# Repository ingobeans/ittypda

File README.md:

# ittyPDA

hi! this is my little thing im working on.

ittyPDA is an itty-bitty PDA/cyberdeck thingy. its smaller than a nintendo ds but has a real keyboard and a full color IPS LCD display, powered by an STM32 microcontroller. its my first ever hardware project and first time designing a pcb !!

it's mainly intended for note-taking/writing, playing silly little videogames, and just being a very hackable little computer.

this repo contains both the hardware designs, under the `ittypda/` subdirectory, as well as the operating system under `ittyOS/`. 3D case files are under `case/`.

## specs & parts

* microprocessor: [STM32F411RET6](https://www.st.com/en/microcontrollers-microprocessors/stm32f411re.html)
    * Up to 100 MHz
    * 512 Kb flash
    * 128 Kb RAM
* display: [3.5" IPS display (no touch version)](https://www.lcdwiki.com/3.5inch_IPS_SPI_Module_ST7796)
* storage: SD card slot included on display
* charging/data transfer possible over USB-C
* battery: 2200mAh LiPo - [this is the one I use, but really any battery with a similar size and connector will work](https://www.amazon.se/-/en/gp/product/B0D7VT93JX?smid=A2YUU8D7JQVZCY&th=1)
* on-board charging circuitry powered by a [BQ24040DSQR](https://www.ti.com/product/BQ24040)
    * also battery level sensing

## download symbols/footprints

to open the kicad project, youll need to download some footprints. my parts are sourced from JLCPCB's parts / LCSC, and you can use [`easyeda2kicad`](https://github.com/uPesy/easyeda2kicad.py) to download LCSC parts to kicad.

the command you need to run is: 

```bash
easyeda2kicad --full --lcsc_id C318884 C191023 C22435642 C13738 C81080 C49023767 C19273152 C165948 C295747 C20416998 C2682616
```

which will download footprints/symbols/3d models for the switches, diodes, etc.

## project status (important !!)

project is in a very early WIP state currently! the PCB is the only truly *finished* part so far.

the case is just a minimum-viable-product for now, and the firmware mostly acts as a proof-of-concept regarding graphics streaming and input handling from the keyboard matrix.

thus the project is mostly about the creation of the PCB, with the case and firmware mostly just acting as beta features used to test the PCB itself.

these features will be developed in the coming months though, and when i have guaranteed that the core PCB does work! this is a project i intend to gradually work on for a long time !

## schematic / PCB

the schematic and PCB are designed in KiCad, files for which are found in `ittypda/`.

the PCB is split in two seperate parts. this is done to achieve a budget 4-layer board, and to get around the fact that JLCPCB's economy PCBA service cant assemble parts on the bottomside of the board.

the mainboard houses the microcontroller, the keypad, and display connector.

the secondary board houses the usb-c port, battery charging ic, voltage regulator, etc.

the two boards mount together like a PCB-sandwich and connect through 7 soldered pads.

showcase how the two boards are mounted:

## firmware - ittyOS

ittyOS is currently in an early proof of concept state, but will have many different apps later on.

implemented:
* display drivers
* reading from microSD card
* streaming image data from microSD to screen
* input from keyboard
* program switching
* basic home screen
* basic notes app

todo:
* improve text input
* usb file transfer
* more apps!
    * wordle
    * journal
* different themes?

### compile ittyOS

the `../firmware` folder contains the low level hardware setup for different boards that can run ittyOS, while `ittyOS/` contains the shared code and the actual system, which is then linked to from the firmware.

you'll need to generate the firmware code from the STM32 project file, since the low-level drivers for these boards are very large and therefore gitignored. you'll need STM32CubeMX. then just open the project file for the firmware you want to build, and hit generate code. 

you'll also have to tell your LSP which CMakeLists you're using.

then, to build, navigate to the firmware you want to build's directory.

1. `cmake --preset Debug` (you only have to run this once)
2. `cmake --build --preset Debug`
3. `STM32_Programmer_CLI -c port=swd -w build/Debug/<DEVBOARD OR ITTYPDA HERE>.elf -v -rst`

## case

the case files are located under `case/`.

the case is designed in,.. blender. its mostly a MVP for a case, and when i get the phyiscal PCB, this and the firmware will be the major focus for the project moving forwards.

most parts are designed to friction-fit, though i wont know how well this works in practice, but will find out soon !

## BOMs

### Final bom (bom.csv)

|Name                         |Cost ($)                              |Source                                                                                           |
|-----------------------------|--------------------------------------|-------------------------------------------------------------------------------------------------|
|PCB                          |13.43                                 |JLCPCB                                                                                           |
|PCB Assembly Fees            |48.21                                 |JLCPCB                                                                                           |
|PCB Assembly Components      |20.55                                 |JLCPCB                                                                                           |
|PCB Shipping                 |24.07                                 | DHL Express                                                                                     |
|Customs & taxes              | 26.56                                |                                                                                                 |
|Total                        |132.77                                |                                                                                                 |

### Parts bom (parts-bom.csv)

|Part Name                    |Description                           |Link                                                                                             |Quantity                                                            |Total Price ($)                                                        |
|-----------------------------|--------------------------------------|-------------------------------------------------------------------------------------------------|--------------------------------------------------------------------|-----------------------------------------------------------------------|
|CL05B104KO5NNNC              |100nF 0402 Ceramic Capacitors         |https://jlcpcb.com/partdetail/1877-CL05B104KO5NNNC/C1525                                         |16                                                                  |0.0864                                                                 |
|CL05A475MP5NRNC              |10V 0402 Ceramic Capacitors           |https://jlcpcb.com/partdetail/24469-CL05A475MP5NRNC/C23733                                       |4                                                                   |0.0828                                                                 |
|CL05C100JB5NNNC              |10pF 0402 Ceramic Capacitors          |https://jlcpcb.com/partdetail/33914-CL05C100JB5NNNC/C32949                                       |4                                                                   |0.0212                                                                 |
|CL05A105KA5NQNC              |1uF 0402 Ceramic Capacitors           |https://jlcpcb.com/partdetail/53938-CL05A105KA5NQNC/C52923                                       |8                                                                   |0.1272                                                                 |
|CL05A225MQ5NSNC              |2.2uF 0402 Ceramic Capacitors         |https://jlcpcb.com/partdetail/13164-CL05A225MQ5NSNC/C12530                                       |2                                                                   |0.0128                                                                 |
|S2B-PH-SM4-TB(LF)(SN)        |PH JST Connector 2mm                  |https://jlcpcb.com/partdetail/JST-S2B_PH_SM4_TB_LF_SN/C295747                                    |2                                                                   |0.427                                                                  |
|1N5819WS                     |Schottky Diodes                       |https://jlcpcb.com/partdetail/GuangdongHottech-1N5819WS/C191023                                  |114                                                                 |1.5504                                                                 |
|05A20L14P                    |FPC Connector                         |https://jlcpcb.com/partdetail/HanElectricity-05A20L14P/C22435642                                 |2                                                                   |0.1404                                                                 |
|TYPE-C-31-M-12               |USB-C Connectors                      |https://jlcpcb.com/partdetail/Korean_HropartsElec-TYPE_C_31_M12/C165948                          |2                                                                   |0.3686                                                                 |
|YLED0603Y                    |Yellow 0603 LED                       |https://jlcpcb.com/partdetail/YONGYUTAI-YLED0603Y/C19273152                                      |20                                                                  |0.13                                                                   |
|0402WGF1002TCE               |10k ohm 0402 Resistor                 |https://jlcpcb.com/partdetail/26487-0402WGF1002TCE/C25744                                        |2                                                                   |0.023                                                                  |
|0402WGF5101TCE               |5.1k ohm 0402 Resistor                |https://jlcpcb.com/partdetail/26648-0402WGF5101TCE/C25905                                        |4                                                                   |0.0268                                                                 |
|0402WGF5100TCE               |510 ohm 0402 Resistor                 |https://jlcpcb.com/partdetail/25866-0402WGF5100TCE/C25123                                        |2                                                                   |0.0122                                                                 |
|0402WGF1001TCE               |1k ohm 0402 Resistor                  |https://jlcpcb.com/partdetail/12256-0402WGF1001TCE/C11702                                        |4                                                                   |0.0392                                                                 |
|0402WGF100JTCE               |10 ohm 0402 Resistor                  |https://jlcpcb.com/partdetail/25820-0402WGF100JTCE/C25077                                        |6                                                                   |0.0342                                                                 |
|TS-1187A-B-A-B               |Tactile Switches                      |https://jlcpcb.com/partdetail/XKBConnection-TS_1187A_B_AB/C318884                                |116                                                                 |2.3664                                                                 |
|MST-12D18G4 SPDT             | Slide Switch                         |https://jlcpcb.com/partdetail/C49023767                                                          |2                                                                   |0.1654                                                                 |
|MAX17048G+T10                |Battery Sense IC MAX17048GT10         |https://jlcpcb.com/partdetail/2777647-MAX17048GT10/C2682616                                      |2                                                                   |4.3212                                                                 |
|BQ24040DSQR                  |Lithium Battery Charge IC BQ24040DSQR |https://jlcpcb.com/partdetail/TexasInstruments-BQ24040DSQR/C81080                                |5                                                                   |2.243                                                                  |
|TLV76133DCYR                 |3.3V Fixed Voltage Regulators - Linear|https://jlcpcb.com/partdetail/TexasInstruments-TLV76133DCYR/C7527500                             |2                                                                   |0.438                                                                  |
|STM32F411RET6                |Microcontroller                       |https://jlcpcb.com/partdetail/STMicroelectronics-STM32F411RET6/C94355                            |2                                                                   |7.7452                                                                 |
|X322516MLB4SI                |16MHz 9pF Crystal Oscillator          |https://jlcpcb.com/partdetail/YXC_CrystalOscillators-X322516MLB4SI/C13738                        |2                                                                   |0.1856                                                                 |

<hr>

<sup>no ai usage</sup>

<sup>made with <3</sup>

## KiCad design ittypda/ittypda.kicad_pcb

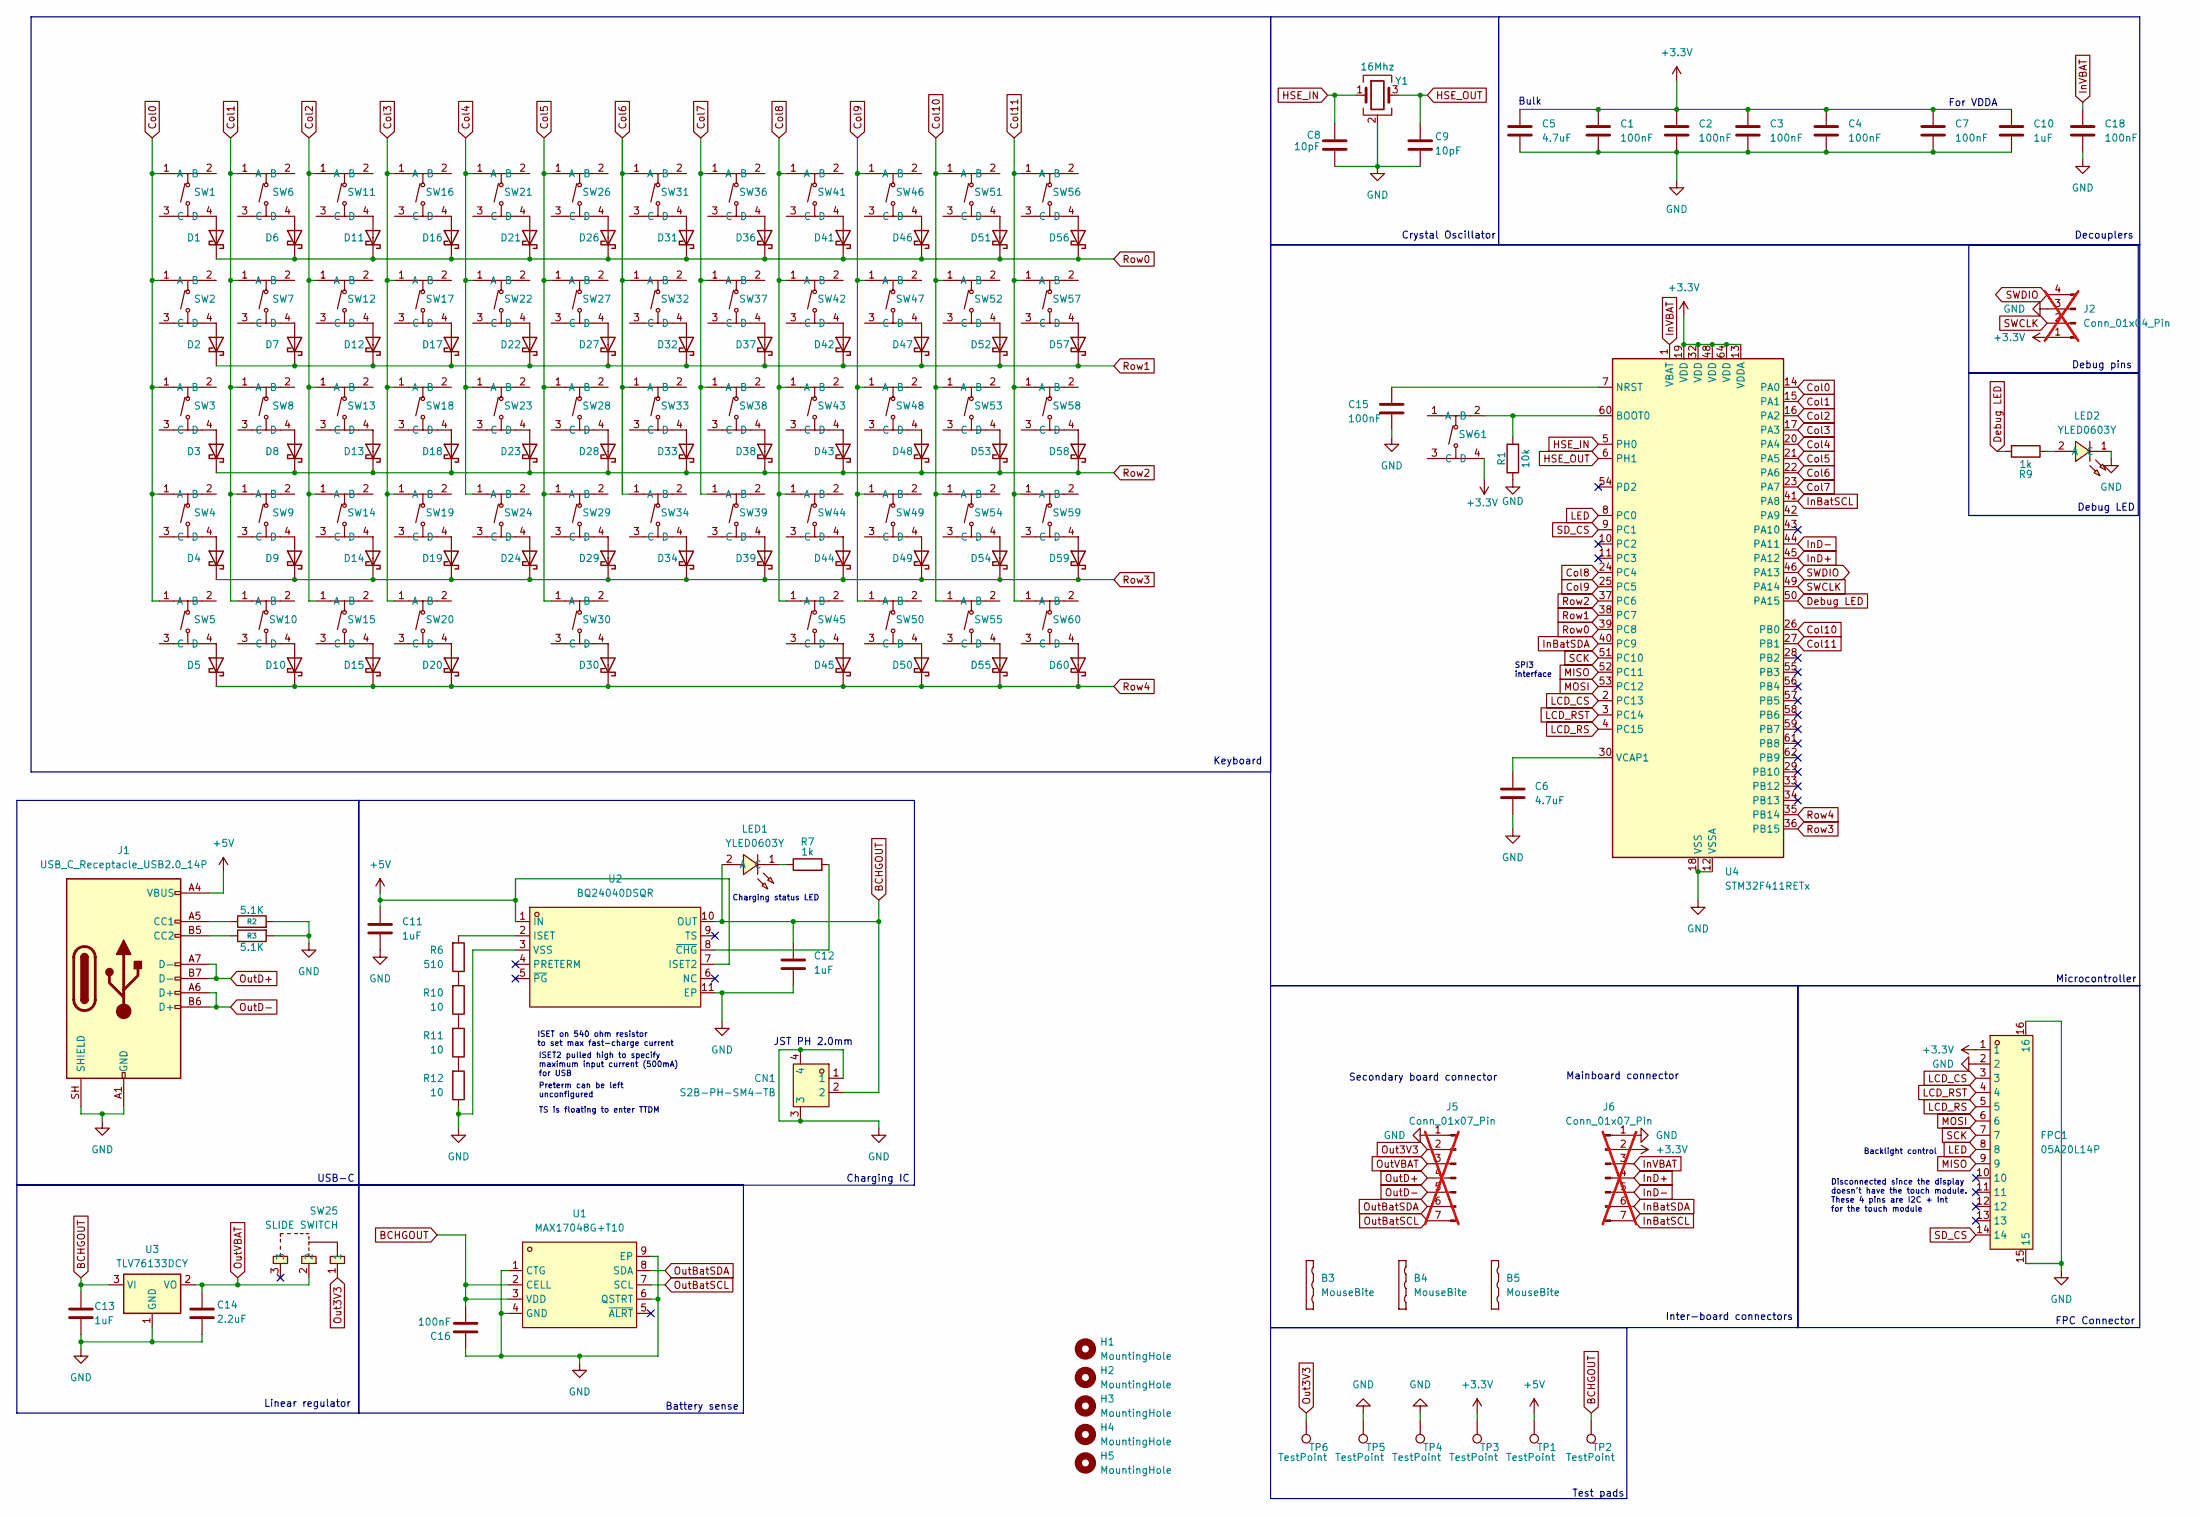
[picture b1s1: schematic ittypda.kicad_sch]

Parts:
B3, B4, B5: MouseBite; mouse-bite-3mm-slot
C1, C2, C3, C4, C7, C15, C16, C18: 100nF; C_0402_1005Metric
C5, C6: 4.7uF; C_0402_1005Metric
C8, C9: 10pF; C_0402_1005Metric
C10, C11, C12, C13: 1uF; C_0402_1005Metric
C14: 2.2uF; C_0402_1005Metric
CN1: S2B-PH-SM4-TB; CONN-SMD_P2.00_S2B-PH-SM4-TB-LF-SN; MPN S2B-PH-SM4-TB(LF)(SN); LCSC Part C295747
D1, D2, D3, D4, D5, D6, D7, D8, D9, D10, D11, D12, D13, D14, D15, D16, D17, D18, D19, D20, D21, D22, D23, D24, D26, D27, D28, D29, D30, D31, D32, D33, D34, D36, D37, D38, D39, D41, D42, D43, D44, D45, D46, D47, D48, D49, D50, D51, D52, D53, D54, D55, D56, D57, D58, D59, D60: 1N5819WS; SOD-323_L1.8-W1.3-LS2.5-RD; Forward Voltage (Vf@If) 600mV@1A; Reverse Voltage (Vr) 40V; Part 1N5819WS; LCSC C191023
FPC1: 05A20L14P; CONN-SMD_05A20L14P; MPN 05A20L14P; LCSC Part C22435642
H1, H2, H3, H4, H5: MountingHole; ToolingHole_1.152mm
J1: USB_C_Receptacle_USB2.0_14P; USB_C_Receptacle_HRO_TYPE-C-31-M-12; LCSC Part C165948
J2: Conn_01x04_Pin; PinHeader_1x04_P2.54mm_Vertical; not fitted
J5, J6: Conn_01x07_Pin; PinHeader_1x07_P2.54mm_Vertical; not fitted
LED1, LED2: YLED0603Y; LED0603-RD-1; MPN YLED0603Y; LCSC Part C19273152
R1: 10k; R_0402_1005Metric
R2, R3: 5.1K; R_0402_1005Metric
R6: 510; R_0402_1005Metric
R7, R9: 1k; R_0402_1005Metric
R10, R11, R12: 10; R_0402_1005Metric
SW1, SW2, SW3, SW4, SW5, SW6, SW7, SW8, SW9, SW10, SW11, SW12, SW13, SW14, SW15, SW16, SW17, SW18, SW19, SW20, SW21, SW22, SW23, SW24, SW26, SW27, SW28, SW29, SW30, SW31, SW32, SW33, SW34, SW36, SW37, SW38, SW39, SW41, SW42, SW43, SW44, SW45, SW46, SW47, SW48, SW49, SW50, SW51, SW52, SW53, SW54, SW55, SW56, SW57, SW58, SW59, SW60, SW61: Switch; SW-SMD_4P-L5.1-W5.1-P3.70-LS6.5-TL_H1.5; MPN TS-1187A-B-A-B; LCSC Part C318884
SW25: SLIDE SWITCH; SW-SMD_MST-12D18G4-SPDT-SLIDE-SWITCH; MPN MST-12D18G2 SMD Slide Switch; LCSC Part C49023767
TP1, TP2, TP3, TP4, TP5, TP6: TestPoint; TestPoint_Pad_D1.5mm
U1: MAX17048G+T10; TDFN-8_L2.0-W2.0-P0.50-BL-EP1.2; MPN MAX17048G+T10; LCSC Part C2682616
U2: BQ24040DSQR; WSON-10_L2.0-W2.0-P0.40-BL-EP; MPN BQ24040DSQR; LCSC Part C81080
U3: TLV76133DCY; SOT-223-3_TabPin2
U4: STM32F411RETx; LQFP-64_10x10mm_P0.5mm
Y1: 16Mhz; CRYSTAL-SMD_4P-L3.2-W2.5-BL

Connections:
+3.3V: C1.1, C2.1, C3.1, C4.1, C5.1, C7.1, C10.1, FPC1.1, J2.1, J6.2, SW61.4 (D), TP3.1 (1_1), U4.13 (VDDA), U4.19 (VDD), U4.32 (VDD), U4.48 (VDD), U4.64 (VDD)
+5V: C11.1, J1.A4 (VBUS), J1.A9 (VBUS), J1.B4 (VBUS), J1.B9 (VBUS), TP1.1 (1_1), U2.1 (IN), U2.7 (ISET2)
BCHGOUT: C12.1, C13.1, C16.2, CN1.2, LED1.2 (A), TP2.1 (1_1), U1.2 (CELL), U1.3 (VDD), U2.10 (OUT), U3.3 (VI)
Col0: SW1.1 (A), SW2.1 (A), SW3.1 (A), SW4.1 (A), SW5.1 (A), U4.14 (PA0)
Col1: SW6.1 (A), SW7.1 (A), SW8.1 (A), SW9.1 (A), SW10.1 (A), U4.15 (PA1)
Col2: SW11.1 (A), SW12.1 (A), SW13.1 (A), SW14.1 (A), SW15.1 (A), U4.16 (PA2)
Col3: SW16.1 (A), SW17.1 (A), SW18.1 (A), SW19.1 (A), SW20.1 (A), U4.17 (PA3)
Col4: SW21.1 (A), SW22.1 (A), SW23.1 (A), SW24.1 (A), U4.20 (PA4)
Col5: SW26.1 (A), SW27.1 (A), SW28.1 (A), SW29.1 (A), SW30.1 (A), U4.21 (PA5)
Col6: SW31.1 (A), SW32.1 (A), SW33.1 (A), SW34.1 (A), U4.22 (PA6)
Col7: SW36.1 (A), SW37.1 (A), SW38.1 (A), SW39.1 (A), U4.23 (PA7)
Col8: SW41.1 (A), SW42.1 (A), SW43.1 (A), SW44.1 (A), SW45.1 (A), U4.24 (PC4)
Col9: SW46.1 (A), SW47.1 (A), SW48.1 (A), SW49.1 (A), SW50.1 (A), U4.25 (PC5)
Col10: SW51.1 (A), SW52.1 (A), SW53.1 (A), SW54.1 (A), SW55.1 (A), U4.26 (PB0)
Col11: SW56.1 (A), SW57.1 (A), SW58.1 (A), SW59.1 (A), SW60.1 (A), U4.27 (PB1)
Debug LED: R9.2, U4.50 (PA15)
GND: C1.2, C2.2, C3.2, C4.2, C5.2, C6.2, C7.2, C8.2, C9.2, C10.2, C11.2, C12.2, C13.2, C14.2, C15.2, C16.1, C18.2, CN1.1, CN1.3, CN1.4, FPC1.2, FPC1.15, FPC1.16, J1.A1 (GND), J1.A12 (GND), J1.B1 (GND), J1.B12 (GND), J1.SH (SHIELD), J2.3, J5.1, J6.1, LED2.1 (C), R1.1, R2.2, R3.2, R12.1, TP4.1 (1_1), TP5.1 (1_1), U1.1 (CTG), U1.4 (GND), U1.6 (QSTRT), U1.9 (EP), U2.3 (VSS), U2.11 (EP), U3.1 (GND), U4.12 (VSSA), U4.18 (VSS), U4.31 (VSS), U4.47 (VSS), U4.63 (VSS), Y1.2 (G), Y1.4 (G)
HSE_IN: C8.1, U4.5 (PH0), Y1.1
HSE_OUT: C9.1, U4.6 (PH1), Y1.3
InBatSCL: J6.7, U4.41 (PA8)
InBatSDA: J6.6, U4.40 (PC9)
InD+: J6.4, U4.45 (PA12)
InD-: J6.5, U4.44 (PA11)
InVBAT: C18.1, J6.3, U4.1 (VBAT)
LCD_CS: FPC1.3, U4.2 (PC13)
LCD_RS: FPC1.5, U4.4 (PC15)
LCD_RST: FPC1.4, U4.3 (PC14)
LED: FPC1.8, U4.8 (PC0)
MISO: FPC1.9, U4.52 (PC11)
MOSI: FPC1.6, U4.53 (PC12)
unnamed: J1.A5 (CC1), R2.1
unnamed: J1.B5 (CC2), R3.1
unnamed: LED1.1 (C), R7.1
unnamed: LED2.2 (A), R9.1
unnamed: R10.1, R11.2
unnamed: R6.1, R10.2
unnamed: R11.1, R12.2
unnamed: D1.2, SW1.4 (D)
unnamed: D2.2, SW2.4 (D)
unnamed: D3.2, SW3.4 (D)
unnamed: D4.2, SW4.4 (D)
unnamed: D5.2, SW5.4 (D)
unnamed: D6.2, SW6.4 (D)
unnamed: D7.2, SW7.4 (D)
unnamed: D8.2, SW8.4 (D)
unnamed: D9.2, SW9.4 (D)
unnamed: D10.2, SW10.4 (D)
unnamed: D11.2, SW11.4 (D)
unnamed: D12.2, SW12.4 (D)
unnamed: D13.2, SW13.4 (D)
unnamed: D14.2, SW14.4 (D)
unnamed: D15.2, SW15.4 (D)
unnamed: D16.2, SW16.4 (D)
unnamed: D17.2, SW17.4 (D)
unnamed: D18.2, SW18.4 (D)
unnamed: D19.2, SW19.4 (D)
unnamed: D20.2, SW20.4 (D)
unnamed: D21.2, SW21.4 (D)
unnamed: D22.2, SW22.4 (D)
unnamed: D23.2, SW23.4 (D)
unnamed: D24.2, SW24.4 (D)
unnamed: D26.2, SW26.4 (D)
unnamed: D27.2, SW27.4 (D)
unnamed: D28.2, SW28.4 (D)
unnamed: D29.2, SW29.4 (D)
unnamed: D30.2, SW30.4 (D)
unnamed: D31.2, SW31.4 (D)
unnamed: D32.2, SW32.4 (D)
unnamed: D33.2, SW33.4 (D)
unnamed: D34.2, SW34.4 (D)
unnamed: D36.2, SW36.4 (D)
unnamed: D37.2, SW37.4 (D)
unnamed: D38.2, SW38.4 (D)
unnamed: D39.2, SW39.4 (D)
unnamed: D41.2, SW41.4 (D)
unnamed: D42.2, SW42.4 (D)
unnamed: D43.2, SW43.4 (D)
unnamed: D44.2, SW44.4 (D)
unnamed: D45.2, SW45.4 (D)
unnamed: D46.2, SW46.4 (D)
unnamed: D47.2, SW47.4 (D)
unnamed: D48.2, SW48.4 (D)
unnamed: D49.2, SW49.4 (D)
unnamed: D50.2, SW50.4 (D)
unnamed: D51.2, SW51.4 (D)
unnamed: D52.2, SW52.4 (D)
unnamed: D53.2, SW53.4 (D)
unnamed: D54.2, SW54.4 (D)
unnamed: D55.2, SW55.4 (D)
unnamed: D56.2, SW56.4 (D)
unnamed: D57.2, SW57.4 (D)
unnamed: D58.2, SW58.4 (D)
unnamed: D59.2, SW59.4 (D)
unnamed: D60.2, SW60.4 (D)
unnamed: R1.2, SW61.2 (B), U4.60 (BOOT0)
unnamed: R6.2, U2.2 (ISET)
unnamed: R7.2, U2.8 (~CHG)
unnamed: C15.1, U4.7 (NRST)
unnamed: C6.1, U4.30 (VCAP1)
Out3V3: J5.2, SW25.1, TP6.1 (1_1)
OutBatSCL: J5.7, U1.7 (SCL)
OutBatSDA: J5.6, U1.8 (SDA)
OutD+: J1.A7 (D-), J1.B7 (D-), J5.4
OutD-: J1.A6 (D+), J1.B6 (D+), J5.5
OutVBAT: C14.1, J5.3, SW25.2, U3.2 (VO)
Row0: D1.1, D6.1, D11.1, D16.1, D21.1, D26.1, D31.1, D36.1, D41.1, D46.1, D51.1, D56.1, U4.39 (PC8)
Row1: D2.1, D7.1, D12.1, D17.1, D22.1, D27.1, D32.1, D37.1, D42.1, D47.1, D52.1, D57.1, U4.38 (PC7)
Row2: D3.1, D8.1, D13.1, D18.1, D23.1, D28.1, D33.1, D38.1, D43.1, D48.1, D53.1, D58.1, U4.37 (PC6)
Row3: D4.1, D9.1, D14.1, D19.1, D24.1, D29.1, D34.1, D39.1, D44.1, D49.1, D54.1, D59.1, U4.36 (PB15)
Row4: D5.1, D10.1, D15.1, D20.1, D30.1, D45.1, D50.1, D55.1, D60.1, U4.35 (PB14)
SCK: FPC1.7, U4.51 (PC10)
SD_CS: FPC1.14, U4.9 (PC1)
SWCLK: J2.2, U4.49 (PA14)
SWDIO: J2.4, U4.46 (PA13)

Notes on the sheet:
For VDDA
Backlight control
ISET on 540 ohm resistor to set max fast-charge current
Disconnected since the display doesn't have the touch module. These 4 pins are I2C + Int for the touch module
Preterm can be left unconfigured
TS is floating to enter TTDM
Secondary board connector
Microcontroller
SPI3 interface
Keyboard
Battery sense
Debug LED
JST PH 2.0mm
USB-C
Test pads
Inter-board connectors
Debug pins
Crystal Oscillator
Linear regulator
Charging IC
Mainboard connector
Decouplers
FPC Connector
ISET2 pulled high to specify maximum input current (500mA) for USB
Charging status LED
Bulk

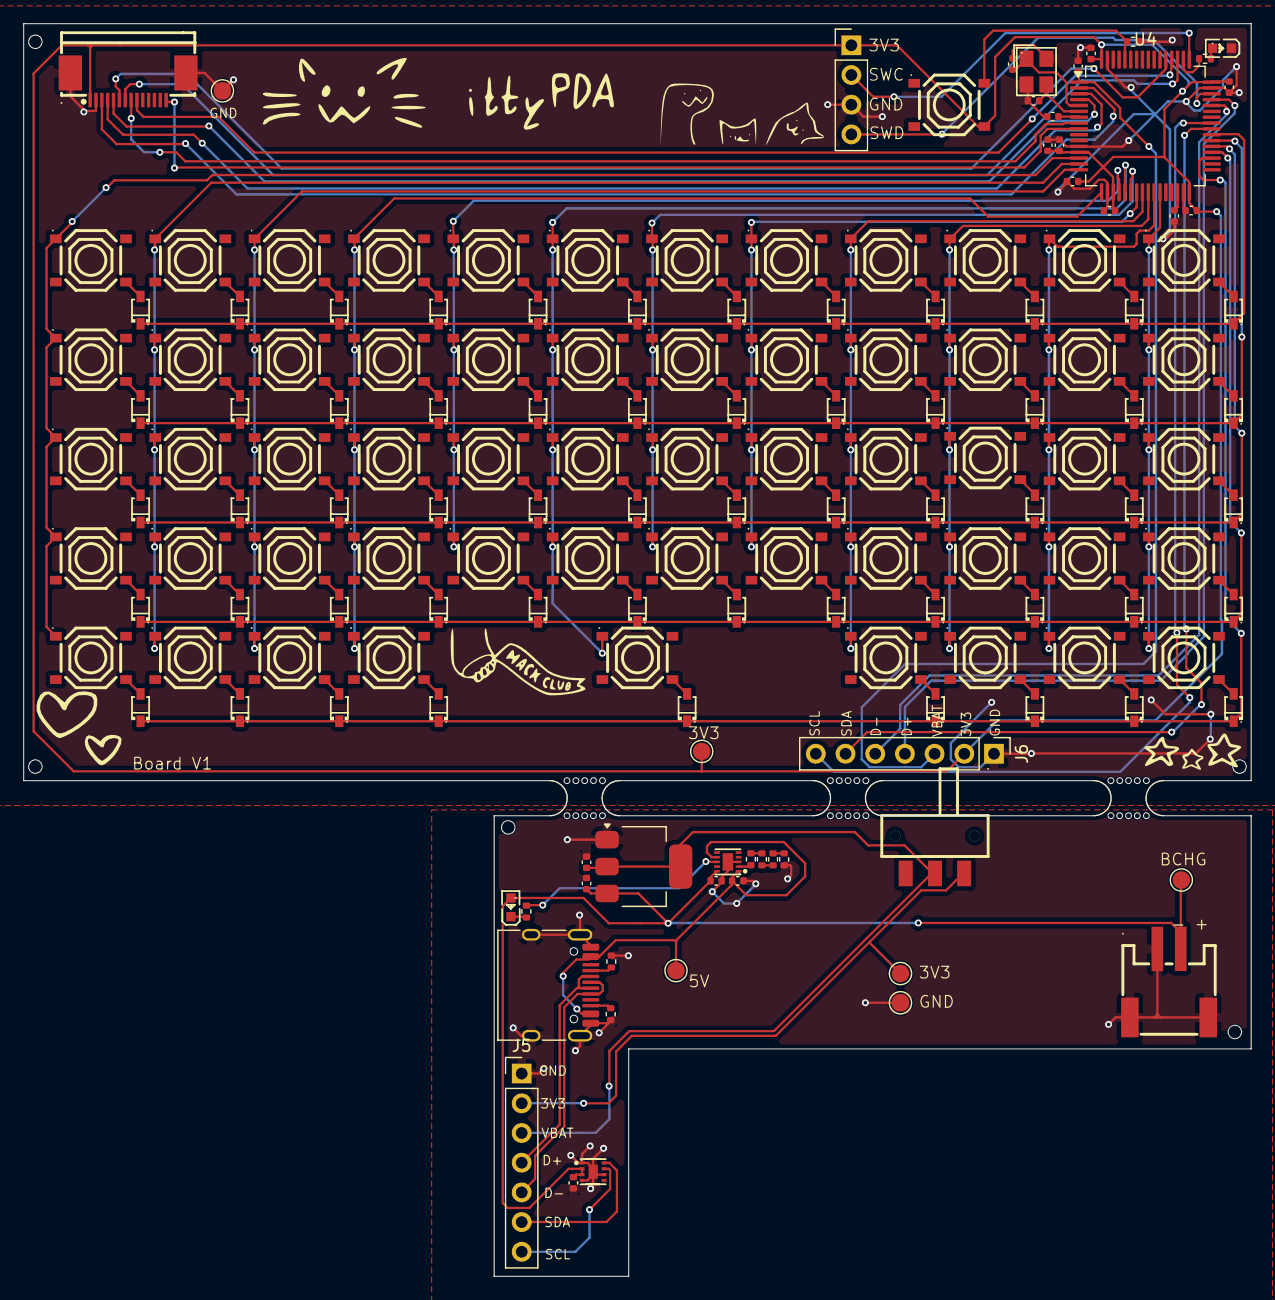
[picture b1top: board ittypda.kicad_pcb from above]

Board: 2 copper layers, 105.0 x 107.2 mm, 169 parts (0 on the bottom side), 114 nets.

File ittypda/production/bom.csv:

Designator,Footprint,Quantity,Value,LCSC Part #
"C1, C2, C3, C4, C7",0402,5,100nF,
C10,0402,1,100uF,
"C11, C12, C13, C14",0402,4,1uF,
C15,0402,1,0.1uF,
C5,0402,1,4.7uF,
C6,0402,1,2.2uF,
"C8, C9",0402,2,10pF,
CN1,CONN-SMD_P2.00_S2B-PH-SM4-TB-LF-SN,1,S2B-PH-SM4-TB,C295747
"D1, D10, D11, D12, D13, D14, D15, D16, D17, D18, D19, D2, D20, D21, D22, D23, D24, D26, D27, D28, D29, D3, D30, D31, D32, D33, D34, D36, D37, D38, D39, D4, D41, D42, D43, D44, D45, D46, D47, D48, D49, D5, D50, D51, D52, D53, D54, D55, D56, D57, D58, D59, D6, D60, D7, D8, D9",SOD-323_L1.8-W1.3-LS2.5-RD,57,1N5819WS,C191023
FPC1,CONN-SMD_05A20L14P,1,05A20L14P,C22435642
J1,USB_C_Receptacle_HRO_TYPE-C-31-M-12,1,USB_C_Receptacle_USB2.0_14P,C165948
"J13, J14",PinHeader_1x05_P2.54mm_Vertical,2,Conn_01x05_Pin,
J2,PinHeader_1x04_P2.54mm_Vertical,1,Conn_01x04_Pin,
LED1,LED0603-RD-1,1,YLED0603Y,C19273152
"MOUSE-BITE-5MM-SLOT_2, MOUSE-BITE-5MM-SLOT",mouse-bite-5mm-slot,2,VAL**,
R1,0402,1,10k,
"R2, R3",0402,2,5.1K,
"R4, R5",0402,2,27,
R6,0402,1,540,
R7,0402,1,1k,
R8,0402,1,1M,
R9,0402,1,200k,
"SW1, SW10, SW11, SW12, SW13, SW14, SW15, SW16, SW17, SW18, SW19, SW2, SW20, SW21, SW22, SW23, SW24, SW26, SW27, SW28, SW29, SW3, SW30, SW31, SW32, SW33, SW34, SW36, SW37, SW38, SW39, SW4, SW41, SW42, SW43, SW44, SW45, SW46, SW47, SW48, SW49, SW5, SW50, SW51, SW52, SW53, SW54, SW55, SW56, SW57, SW58, SW59, SW6, SW60, SW61, SW7, SW8, SW9",SW-SMD_4P-L5.1-W5.1-P3.70-LS6.5-TL_H1.5,58,Switch,C318884
SW25,SW-SMD_MST-12D18G4-SPDT-SLIDE-SWITCH,1,SLIDE SWITCH,C49023767
U1,LQFP-64_10x10mm_P0.5mm,1,STM32F401RETx,
U2,WSON-10_L2.0-W2.0-P0.40-BL-EP,1,BQ24040DSQR,C81080
U3,WSON-6-1EP_2x2mm_P0.65mm_EP1x1.6mm,1,TLV75801PDRV,
Y1,CRYSTAL-SMD_4P-L3.2-W2.5-BL,1,16Mhz,C13738

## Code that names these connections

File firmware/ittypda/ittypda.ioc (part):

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Mcu.Name=STM32F411R(C-E)Tx
Mcu.Package=LQFP64
Mcu.UserName=STM32F411RETx
PA0-WKUP.Signal=GPIO_Output
PA1.Signal=GPIO_Output
PA11.Mode=Device_Only
PA11.Signal=USB_OTG_FS_DM
PA12.Mode=Device_Only
PA12.Signal=USB_OTG_FS_DP
PA13.Mode=Serial_Wire
PA13.Signal=SYS_JTMS-SWDIO
PA14.Mode=Serial_Wire
PA14.Signal=SYS_JTCK-SWCLK
PA2.Signal=GPIO_Output
PA3.Signal=GPIO_Output
PA4.Signal=GPIO_Output
PA5.Signal=GPIO_Output
PA6.Signal=GPIO_Output
PA7.Signal=GPIO_Output
PA8.Mode=I2C
PA8.Signal=I2C3_SCL
PB0.Signal=GPIO_Output
PB1.Signal=GPIO_Output
PB14.GPIOParameters=GPIO_PuPd
PB14.GPIO_PuPd=GPIO_PULLDOWN
PB14.Signal=GPIO_Input
PB15.GPIOParameters=GPIO_PuPd
PB15.GPIO_PuPd=GPIO_PULLDOWN
PB15.Signal=GPIO_Input
PC0.Signal=GPIO_Output
PC1.Signal=GPIO_Output
PC10.Mode=Full_Duplex_Master
PC10.Signal=SPI3_SCK
PC11.Mode=Full_Duplex_Master
PC11.Signal=SPI3_MISO
PC12.Mode=Full_Duplex_Master
PC12.Signal=SPI3_MOSI
PC13-ANTI_TAMP.Signal=GPIO_Output
PC14-OSC32_IN.Signal=GPIO_Output
PC15-OSC32_OUT.Signal=GPIO_Output
PC4.Signal=GPIO_Output
PC5.Signal=GPIO_Output
PC6.GPIOParameters=GPIO_PuPd
PC6.GPIO_PuPd=GPIO_PULLDOWN
PC6.Signal=GPIO_Input
PC7.GPIOParameters=GPIO_PuPd
PC7.GPIO_PuPd=GPIO_PULLDOWN
PC7.Signal=GPIO_Input
PC8.GPIOParameters=GPIO_PuPd
PC8.GPIO_PuPd=GPIO_PULLDOWN
PC8.Signal=GPIO_Input
PC9.Mode=I2C
PC9.Signal=I2C3_SDA
PH0\ -\ OSC_IN.Mode=HSE-External-Oscillator
PH0\ -\ OSC_IN.Signal=RCC_OSC_IN
PH1\ -\ OSC_OUT.Mode=HSE-External-Oscillator
PH1\ -\ OSC_OUT.Signal=RCC_OSC_OUT
RCC.HSE_VALUE=16000000
RCC.SYSCLKFreq_VALUE=84000000
RCC.SYSCLKSource=RCC_SYSCLKSOURCE_PLLCLK
board=custom

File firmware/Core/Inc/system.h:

#define VERSION "0.3.1"

#include "main.h"

#define LCD_CS GPIO_PIN_13  // C
#define LCD_RST GPIO_PIN_14 // C
#define LCD_RS GPIO_PIN_15  // C

#define LED GPIO_PIN_0 // C

// #define MOSI GPIO_PIN_12 // C
// #define MISO GPIO_PIN_11 // C
// #define SCK GPIO_PIN_12 // B

#define SD_CS GPIO_PIN_1 // C

#define HSPI hspi3

void update();
void init();

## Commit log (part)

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2026-06-22 add switches to schematic
2026-06-23 add internal parts to mockup
2026-06-24 work on PCB
2026-06-24 migrate all parts to easyeda2kicad footprints
2026-06-24 fix decal on mockup
2026-06-24 colorcode keys on keyboard and fix layout
2026-06-24 replace connector with proper one
2026-06-24 add readme
2026-06-25 add decouplers and switches for boot0 and nrst
2026-06-25 rename project files
2026-06-25 add crystal oscillator
2026-06-25 add usb-c connector
2026-06-25 change stm microcontroller
2026-06-25 clean up usb
2026-06-25 add no-connects to the 4 touch pins of the FPC connector
2026-06-25 add cool render
2026-06-25 reorganize schem
2026-06-25 add more items to gitignore
2026-06-25 remove render folder from git tracked
2026-06-25 add BQ24040 charging IC
2026-06-26 add linear regulator.. we have power!!!
2026-06-26 wire up VBAT
2026-06-26 add JST connector
2026-06-26 fix JST connector side
2026-06-26 organize schem
2026-06-26 replace all old switch symbols
2026-06-26 add labels to FPC connector pins
2026-06-26 add debug pins
2026-06-26 connect FPC pins to ic gpios
2026-06-26 add stm32cubemx project files
2026-06-26 add debug pins footprint
2026-06-26 connect keyboard matrix pins to GPIO
2026-06-26 add a power slide switch that cuts off 3v3 and also removed the NRST switch
2026-06-26 fix slide switch
2026-06-26 use bigger footprint for slide switch
2026-06-26 add values and footprint for charging status LED
2026-06-26 update readme!!
2026-06-26 use set height for banner to avoid text moving around when it loads
2026-06-27 update gitignore
2026-06-27 add todo
2026-06-28 assign footprints!!
2026-06-28 layout keyboard in pcb (not accurate spacings, and no diodes)
2026-06-28 place all caps and resistors (not final positions)
2026-06-28 add 3d model for usb c port and finalize initial placement of parts (not diodes yet)
2026-06-29 snap all keys to grid
2026-06-29 placed all switch diodes!
2026-06-29 layout front side of board
2026-06-29 split power circuitry into seperate PCB part
2026-06-29 add mouse bites
2026-06-29 move mousebites to bottom of pcb
2026-06-29 add gap for wires to connect through
2026-06-30 wire keyboard matrix switches
2026-06-30 connect rows of keyboard matrix to microcontroller
2026-06-30 wire columns to mc
2026-06-30 wire fpc connector
2026-06-30 change connector type between the two pcbs and wire it up on the mainboard
2026-06-30 align connectors between boards (secondary board is flipped)
2026-06-30 increase battery margin
